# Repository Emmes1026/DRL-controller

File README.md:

# DRL-controller
KiCad schematic for a custom PCB that automatically turns on daytime running lights when the car starts.

# Project Overview
This repository contains the KiCad schematic and PCB layout for a custom Automatic Daytime Running Lights (DRL) controller. It is a personal DIY project designed to automatically turn on the car's DRLs when the vehicle is turned on, without the need for manual switching.

# How It Works
The circuit is designed to detect when the car is running and activate the lights accordingly.

# Schematic Notes
Please note that the schematic image contains labels in Polish.

* s_d - DRL.
* kontrolka s_d - DRL indicator.
* swiatla_post - parking light.

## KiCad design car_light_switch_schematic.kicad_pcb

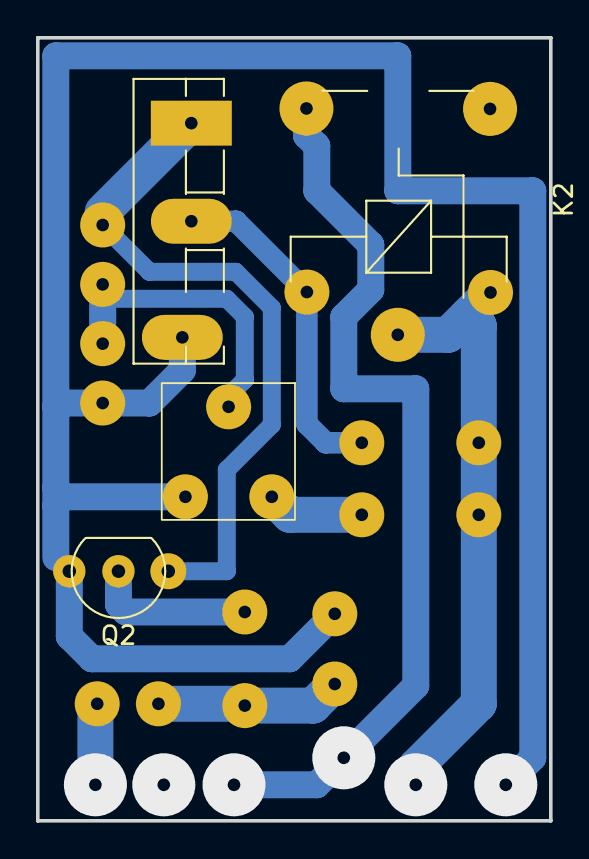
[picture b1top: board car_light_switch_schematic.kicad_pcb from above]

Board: 2 copper layers, 28.5 x 43.5 mm, 11 parts (0 on the bottom side), 8 nets.

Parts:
C1: 2,2 uF 50V; Resistor_1K_moj
D1: C13V; Resistor_1K_moj
D2, D3: 1N4004; Resistor_1K_moj
K2: SANYOU_SRD_Form_C; Relay_moj_schemat
Q1: 2SD1047; TO-3PB-3_Vertical
Q2: BC547; TO-92_Inline
R1: 1K; Resistor_1K_moj
R2: 5.6K; Resistor_1K_moj
R3: 470; Resistor_1K_moj
RV1: 10K; RV1

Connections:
+12V 30: D1.1 (K), D2.1 (K), K2.1, K2.2
GND 85: C1.2, Q1.3 (E), Q2.3 (E), R3.1, RV1.3
unnamed: C1.1, R1.1, RV1.2
unnamed: D1.2 (A), RV1.1
unnamed: D2.2 (A), K2.5, Q1.2 (C)
unnamed: R2.2, R3.2
unnamed: Q1.1 (B), Q2.1 (C), R1.2
unnamed: Q2.2 (B), R2.1

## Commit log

2026-04-08 Expand README with project details and functionality
    Added project overview and explanation of functionality.
2026-04-08 Update README with schematic notes
    Added schematic notes and labels in Polish to README.
2026-04-08 Fix formatting of schematic notes in README
2026-04-08 Update schematic notes with bullet points
